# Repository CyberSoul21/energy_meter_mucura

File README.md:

# energy_meter_mucura
Year: December - 2019
Device for measuring energy electricity consumption. The device measure and display the current accumulative power consumption on a LCD.

Video: https://www.youtube.com/watch?v=3Hr1MzA0mfI

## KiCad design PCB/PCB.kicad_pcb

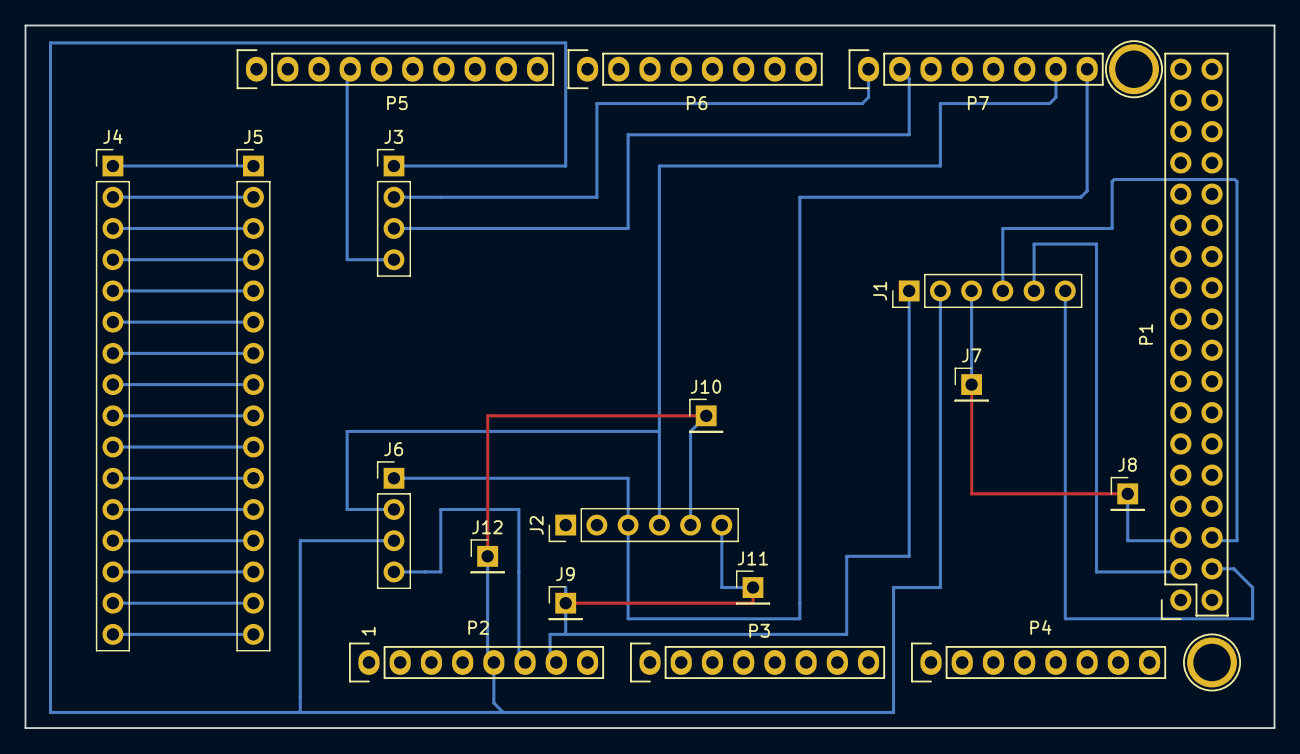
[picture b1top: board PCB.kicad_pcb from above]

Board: 2 copper layers, 101.6 x 57.1 mm, 21 parts (0 on the bottom side), 26 nets.

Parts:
J1: memory_SD; PinHeader_1x06_P2.54mm_Vertical
J2: RTC; PinHeader_1x06_P2.54mm_Vertical
J3: sensor; PinHeader_1x04_P2.54mm_Vertical
J4: I2C_pins_interfaces; PinHeader_1x16_P2.54mm_Vertical
J5: pins_LCD; PinHeader_1x16_P2.54mm_Vertical
J6: I2C_interface; PinHeader_1x04_P2.54mm_Vertical
J7, J8, J9, J10, J11, J12: Aux; PinHeader_1x01_P2.54mm_Vertical
P1: Digital; Socket_Strip_Arduino_2x18
P2: Power; Socket_Strip_Arduino_1x08
P3, P4: Analog; Socket_Strip_Arduino_1x08
P5: PWM; Socket_Strip_Arduino_1x10
P6: PWM; Socket_Strip_Arduino_1x08
P7: Communication; Socket_Strip_Arduino_1x08
P10, P13: CONN_01X01; Arduino_1pin

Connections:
+5V: J1.2, J2.5, J3.1, J6.3, J10.1, J12.1, P1.35, P1.36, P2.5
/14(Tx3): J3.2, P7.1
/15(Rx3): J3.3, P7.2
/20(SDA): J2.4, J6.2, P7.7
/21(SCL): J2.3, J6.1, P7.8
/50(MISO): J1.3, J7.1, J8.1, P1.5
/51(MOSI): J1.4, P1.6
/52(SCK): J1.5, P1.3
/53(SS): J1.6, P1.4
/DP0: J4.7, J5.7
/DP1: J4.8, J5.8
/DP2: J4.9, J5.9
/DP3: J4.10, J5.10
/DP4: J4.11, J5.11
/DP5: J4.12, J5.12
/DP6: J4.13, J5.13
/DP7: J4.14, J5.14
/Enable: J4.6, J5.6
/LEDN: J4.16, J5.16
/LEDP: J4.15, J5.15
/RW: J4.5, J5.5
/RegSE: J4.4, J5.4
/VDD: J4.2, J5.2
/VE: J4.3, J5.3
/VSS: J4.1, J5.1
GND: J1.1, J2.6, J3.4, J6.4, J9.1, J11.1, P1.1, P1.2, P2.6, P2.7, P5.4
